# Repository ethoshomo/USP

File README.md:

# USP

Algoritmos e trabalhos apresentados durante Graduação em Ciência da Computação na USP - São Carlos.

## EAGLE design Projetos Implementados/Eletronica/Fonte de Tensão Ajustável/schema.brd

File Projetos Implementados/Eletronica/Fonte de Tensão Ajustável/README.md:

# 
# SSC0180-Eletronica-p1-Fonte de Tensão Ajustável 3V - 12V

Apresentação sobre a fonte de Tensão Ajustável, com amperagem máxima de 100mA.
## Integrantes: 
- Arthur Vergaças Daher Martins, nUSP: 12542672
- Carlos Filipe de Castro Lemos, nUSP: 12542630
- Laís Saloum Deghaide, nUSP: 11369767
- Rafael Zimmer, nUSP: 12542612

## [Video Explicativo](https://drive.google.com/file/d/1rR6jG3XRCm0vJ2gCErPLd6zFY5oDtITS/view)
(Obs: Slide do Transformador -> Na hora da explicação, foi dito que havia 179 bobinas no lado com menos bobinas , porém foi invertido por conveniência, pois o transformador está ao contrário de como está no Falstadt)
## [Slides Explicativos](https://docs.google.com/presentation/d/16bPbDchU_gi0e6y3p-GB68edqlrLqPZabgu-Sr-JJxo/edit?usp=sharing)

## Introdução
De acordo com as orientações de aula, o presente trabalho deveria consistir na elaboração de uma fonte de tensão ajustável (3V a 12V) com capacidade de 100mA.
Os alunos deveriam fazer um projeto que englobasse um diagrama da fonte, valores dos componentes escolhidos e uma lista de componentes (contendo valores e preços). Além disso, deveria acompanhar o trabalho um vídeo explicativo e um projeto esquemático no programa EAGLE.
Em ordem, apresentaremos os componentes utilizados no circuito elétrico, buscando responder qual a função de cada um, em que porção se localizam, bem como qual o respectivo comportamento na fonte, mostrando sua influência sobre a voltagem ou sobre a corrente elétrica.

### Visão Geral da Fonte de Tensão Ajustável
- Esquemático:

### Parte da Entrada da Fonte: Tensão A/C

Especificações da Tensão A/C no circuito:
- Voltagem de pico: 
Vpico = RMS * √2

Frequência e Deslocamento de Fase:
- Ambos os valores são tabelados, em São Paulo são 60Hz e 120°, que é a tensão referência para a elaboração deste trabalho.

### Parte do Transformador (Transformer)
- **Finalidade**: o componente “transformador” realiza a modificação da tensão de entrada por outra previamente calculada (seja sentido direto ou indireto); ou seja, para o presente trabalho, reduz a tensão de entrada (127V) para uma menor (aproximadamente 18V).

### Parte do Transformador (Transformer) - Cálculos

- A transformação de tensão no transformador acontece por meio eletromagnético, sendo certo que, em razão dos materiais usados na sua produção (liga de aço-silício), não apresenta dados significativas perdas de energia (por efeito Joule ou por correntes parasitas).
- Como desejamos diminuir o valor da tensão, foi preciso calcular a razão entre a tensão de saída (18.8V) pela tensão de entrada (179V) de modo a escolher o transformador adequado.
- Esclareça-se que o valor de tensão de entrada foi calculado no passo anterior, enquanto que o valor de saída foi superior a 12V porque há outros componentes na fonte que consomem voltagem, além da saída. 
Assim, temos que a razão entre os inputs do transformador é:

### Parte do Retificador de Onda Completa (Rectifier)
- **Finalidade**: a porção “retificadora de onda completa” recebe a tensão alternada proveniente do transformador e a modifica em onda pulsante unidirecional dentro do circuito eletrônico (isto é, com ripple). Esse passo é realizado pela ponte de diodo, que coordena a entrada de corrente no circuito. 

Antes da retificação:

Depois da retificação:	

Representação da ponte de diodo:

### Parte do Retificador (Rectifier) - Cálculos
- Na porção retificadora, teremos uma alternância de corrente elétrica alternada na ponte de diodos, o que faz a ativação de dois diodos por vez (ligados em série). 
- Assim, os valores das resistências serão somados e irão gerar uma perda aproximada de 0.7V por cada um. Logo, teremos um total de 1,4V dissipados.
- Tensão de ativação dos diodos: 
Va x Nd = 0.7V x 2 = **1,4V.**
**Va** = Voltagem de ativação dos diodos
**Nd** = Número de diodos

### Parte da Filtragem (Smoothing)

- **Finalidade**: objetiva suavizar as pulsões da tensão. É realizada pela ação de um capacitor eletrolítico ligado em paralelo com a fonte supridora de energia. Após carregado por completo (com a voltagem máxima), ele supre momentaneamente o circuito com corrente elétrica quando a onda reflete a diminuição na voltagem de entrada.

### Parte da Filtragem (Smoothing) - Cálculos

- Na porção de filtragem, foi necessário realizar os cálculos referentes ao capacitor que deveríamos utilizar para “linearizar” o ripple. 
- Utilizamos a fórmula para um ripple de 10%:

- C = Capacitância do Capacitor (F)
	Io = Corrente de Saída (A)
	Vs = Voltagem de Chegada (V)
	f = Frequência (Hz)

- Observação: no circuito eletrônico, optamos por um valor maior do que o calculado para garantir o suprimento necessário de corrente elétrica quando o pulso diminui sua voltagem e por ser mais comum no mercado.

### Parte da Regulagem (Regulator)

- **Finalidade**: recebe a corrente retificada bem como suaviza e modela a tensão de saída mantendo-a estável, embora haja variações na corrente elétrica. 
- É a porção mais complexa do circuito, englobando como componentes principais um potenciômetro, um diodo zener e um transistor.

## Circuito no Falstad

[Clique aqui para abrir](https://www.falstad.com/circuit/circuitjs.html?ctz=CQAgzCAMB0l3BWEDoBYEE4AcBGBcwwdVUAmVEANkmRFQgQFMBaHHAKADdwxKQsahPqUhYoIHFRo4A7BnGlYGehgQ5IpMBiKqIMBOwDuPPgPCUxZyEZMgRY3mPtR2AFXOWaqHMNHiKMOpIzDCQmKhhMqgyCEQ4mspIWNCUMryyYHJYWBFgTKxiMBjFNt6+YtGkdn7WxpXVFTJVxAHsACZ0TRIkyJAUbFVVbYwAZgCGAK4ANgAu7ci83RT4-fF2IMPj03MdKxIyfPUt65uTs-N7snyxfMdDo2dzxjdLC6Y0tW-8Xj7fLs99CRrahiAb-Xr9A5SUFQ6wAY2hQKqIP2fA+sEQt0o0Aw6nQRFIAlkAhkUAxHGMKLBKKsNipUJRzk+jL8FhoTPYYAoAC9GAA7RgAJ1Yegk0BkxDyhJwGGl8FILFJ7IkenY3KoZmcbJVwhAvIFwpwYDpZjMNI+7EFGpoZrMRrREngJukizSt0W1lkFDdOpAB1BFgkvTgZMQIAASowAM4ASyjMzGfLhjEtfsWPjEPqZdhEnyzrM1NRs+c8TiLMz9gbwVQEoIQVWkIGYqFgOCwCCa2kouMopAb4uIchkWG0xGKUsdNFO21TtYkgbn2finzn9u+nnBc9tNotAHN1w1+JQKNnrAB7Oyk4-+SDFapkhvrUik41AA)

## Circuito no EAGLE

Para construção do board PCB foi primeiro esquematizado o circuito com componentes no Eagle, em seguida gerado o board e organizado os componentes:

## Preço das Peças

| Componente | Especificação | Quantidade | Função | Preço (unidade) |
| ------ | ------ | ------ | ------ | ------ |
| [Transformador]() | 18V e 500mA | 1 | Reduz a tensão de entrada | R$ 27,99 |
| [Diodo]() | 600V e 1A | 4 | Retifica a tensão | R$ 0.19 |
| [Capacitor]() | 560μF | 1 | Reduz a tensão à um ripple específico | R$ 1.99 |
| [Diodo Zener]() | 13V e 0.5W | 1 | Linearizar o ripple | R$ 0.19 |
| [Transistor]() | 1A | 1 | Regula a tensão máxima de saída | R$ 0.29 |
| [Potenciômetro]() | 5KΩ | 1 | Regula a corrente para ativação do transistor | R$ 2.21 |
| [Resistor]() | 1KΩ | 1 | Limita e proteje a corrente no diodo zener | R$ 0.05 |
| [Resistor]() | 2.2KΩ | 1 | Compete com a corrente mínima, especificando a tensão de saída mínima | R$ 0.05 |
**Total: R$ 32.96**

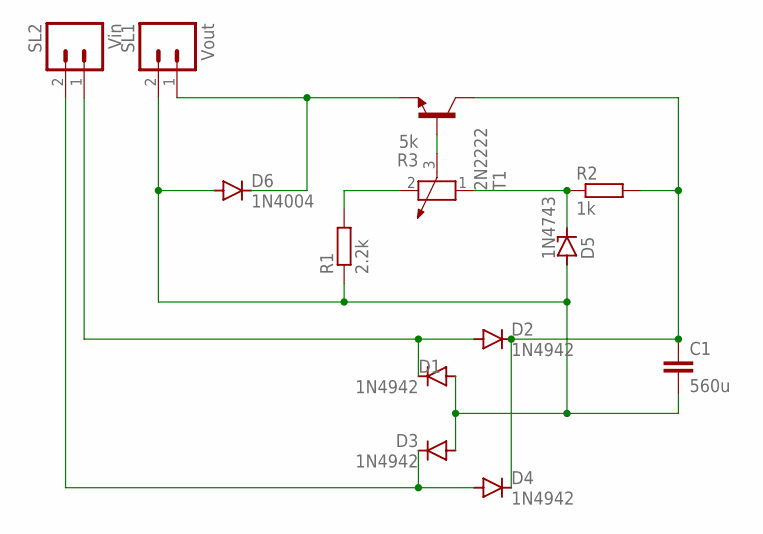
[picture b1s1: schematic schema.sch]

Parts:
C1: 560u; C025-025X050
D1, D2, D3, D4: 1N4942; DO41-10
D5: 1N4743; DO41Z10
D6: 1N4004; DO41-10
R1: 2.2k; 0204/7
R2: 1k; 0204/7
R3: 5k; PT-10
SL1: Vout; 02P
SL2: Vin; 02P
T1: 2N2222; TO18

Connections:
unnamed: D6.C, SL1.1, T1.1 (E)
unnamed: C1.2, D1.A, D3.A, D5.A, D6.A, R1.1, SL1.2
unnamed: D5.C, R2.1, R3.1
unnamed: R1.2, R3.2
unnamed: R3.3, T1.2 (B)
unnamed: D3.C, D4.A, SL2.2
unnamed: C1.1, D2.C, D4.C, R2.2, T1.3 (C)
unnamed: D1.C, D2.A, SL2.1

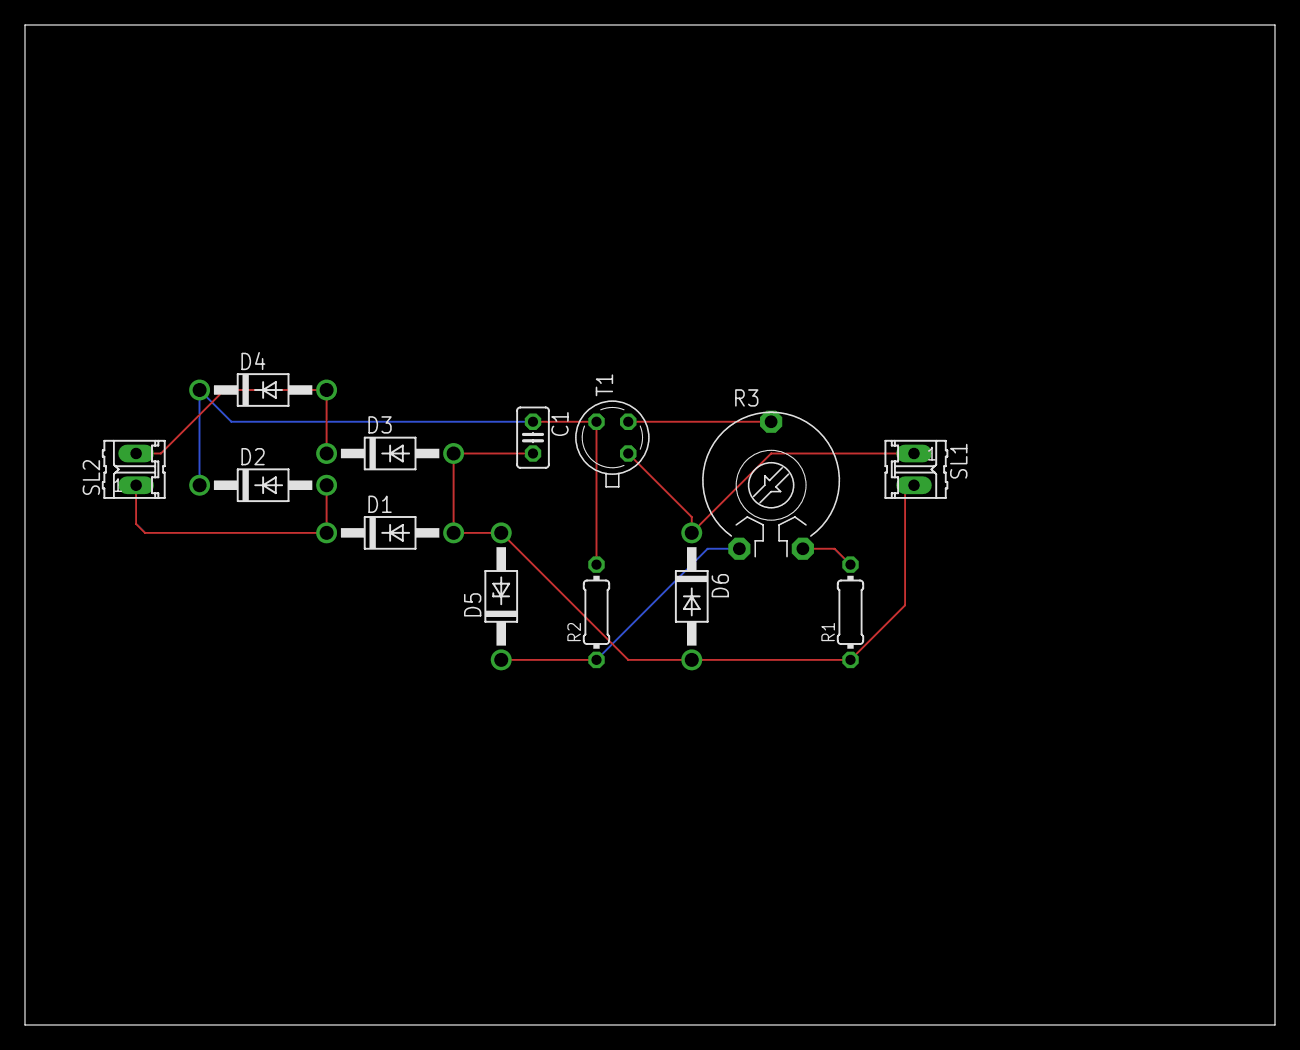
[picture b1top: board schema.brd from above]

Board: 2 copper layers, 100.0 x 80.0 mm, 13 parts (0 on the bottom side), 8 nets.

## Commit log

2022-02-22 Atualizando Readme
